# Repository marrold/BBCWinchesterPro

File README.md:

# BBCWinchesterPro

A PCB that combines a Raspberry Pi running [PiTubeDirect](https://github.com/hoglet67/PiTubeDirect) and a J.G Harston's [IDE Interface](https://mdfs.net/Info/Comp/BBC/IDE/), intended to emulate the 6502 2nd Processor and Winchester Hard Disk required to run a Level 3 Econet Fileserver on a BBC Micro Model B.

The current revision was designed to test if the theory works rather than a finished product. The long term goal is to place it in a suitably 80's looking enclosure which will probably require some changes to the overall size and mounting holes but perhaps in the meantime the schematics and PCB will be useful to someone.

The schematic is included as a [PDF](Schematic.pdf)

## Whats the ATTiny MCU for?

PiTubeDirect *toggles* the Pi's onboard LED when the Tube is accessed, however I'd like an external LED to pulse with activity. The ATTiny detects a rising or falling edge and pulses the LED for 50ms.

To use this feature you'll need to program the ATTiny and use the [Indigo Alpha 4](https://github.com/hoglet67/PiTubeDirect/releases/tag/indigo-alpha4) revision of PiTubeDirect which supports re-mapping the activity to another GPIO.

Add the following to the end of `cmdline.txt`:
`bcm2708.disk_led_gpio=16`

This is somewhat experimental, the code is crude, and I'm not entirely sure if its detecting every edge when the Tube is at full tilt, but it makes the LED blink convincingly   so its good enough for my requirements.

If you don't want to bother with it, you can bridge pins 2 and 3 of the U5 footprint, indicated on the silkscreen.

## Usage

- It's *highly recommended* to use a 2GB CF Card as modified tools exist to deal with a disc this size
- For information on setting up and using PiTubeDirect, see the projects detailed [Wiki](https://github.com/hoglet67/PiTubeDirect/wiki)
- To use the IDE interface you'll need version [ADFS  v1.33](https://mdfs.net/System/ROMs/Filing/Disk/Acorn/ADFS133) which has been patched for IDE support.
- I also recommend using patched versions of [HDInit](https://mdfs.net/Info/Comp/BBC/IDE/HDInit) and [WFSInit](https://stardot.org.uk/forums/viewtopic.php?p=411297#p411297) that can handle larger discs.
- For instructions on formatting the CF card see the [Wiki](https://github.com/marrold/BBCWinchesterPro/wiki/Formatting-the-Hard-Disk)
- For instructions on setting up the Econet partition, also see the [Wiki](https://github.com/marrold/BBCWinchesterPro/wiki/Initialising-the-Disk-for-a-Level-3-Econet-Fileserver)

## Parts Required

- [PCI slot IDE to Compact Flash Adapter](https://www.amazon.co.uk/gp/product/B0913811PP)
- Raspberry Pi + SD Card
- 5x 0.1uF ceramic capacitors with a 5mm pitch
- 2x 22uF electrolytic capacitors with a 2mm pitch
- 3x 1k 1/4w resistors
- 3x LEDs and suitable 1/4w resistors
- 2x [SN74LVC245AN](http://d.digikey.com/dc/mn-w0iJh4uEE_bUitNCuXpPSTLmwSDrmPaa_ksuLmn07WQWvHI6vieAM8l8Rz71y9-o2iqNxD_lrRHs2f6p78UOWSMZi80Re0OX4QjTHXhzXzyCP1n-WYmlf5x2yjzHYfHzZC5O6tAVstkKuOzoHwbgnRBw45ztk-WaaeLEz83g=/MDI4LVNYSy01MDcAAAGQeWyQoGkputw3nr4VpWGkNsxv4PB3VXIkOks0B2FcjYxorqdoh39jE906jV2IX0SxzNbf8sc=)
- 1x [SN74LS02N](http://d.digikey.com/dc/mn-w0iJh4uEE_bUitNCuXpPSTLmwSDrmPaa_ksuLmn07WQWvHI6vieAM8l8Rz71y9-o2iqNxD_lrRHs2f6p78bnTDQXV0_ONXEKM5iC55d-ZDkkt9n89zQITQIYKv5ImfzPp6AZ2aezEFJFPNdnpA2yuf_bsGcfQkRQfUysnwfE=/MDI4LVNYSy01MDcAAAGQeWyQoGkputw3nr4VpWGkNsxv4PB3VXIkOks0B2FcjYxorqdoh39jE906jV2IX0SxzNbf8sc=)
- 1x [SN74LS139AN](http://d.digikey.com/dc/mn-w0iJh4uEE_bUitNCuXpPSTLmwSDrmPaa_ksuLmn07WQWvHI6vieAM8l8Rz71y9-o2iqNxD_lrRHs2f6p78ZChZSCAtt8kdLK_f7oz0DTUWDhmkEZ-6cGHutOkHit2hcfdb0F0ck6e2jeWpSL4i42dJ505bw-7yi25-H_klbc=/MDI4LVNYSy01MDcAAAGQeWyQoGkputw3nr4VpWGkNsxv4PB3VXIkOks0B2FcjYxorqdoh39jE906jV2IX0SxzNbf8sc=)
- 1x [ATTINY85-20PU](http://d.digikey.com/dc/mn-w0iJh4uEE_bUitNCuXpPSTLmwSDrmPaa_ksuLmn3wb489Ozp7P-auFeMYVOl116EiIEbZ38BDQy1OX_LrrLPV3Ec8LFvckgIt5WBiMOWBzA2AtKbyb9r8UKNGoR5mw2eYflZHiaYFx4eLpeBZ2Q5_0KFzTh_zHWoZHqgDAwE=/MDI4LVNYSy01MDcAAAGQeWyQoGkputw3nr4VpWGkNsxv4PB3VXIkOks0B2FcjYxorqdoh39jE906jV2IX0SxzNbf8sc=)
- 2x 20 pin DIP sockets
- 1x 16 pin DIP socket
- 1x 14 pin DIP socket
- 1x 4 pin DIP socket
- 1x 40 Pin, 2.54 pitch Male Shrouded + Keyed connector
-  1x 34 Pin, 2.54 pitch  Male Shrouded + Keyed connector
- 1x 40 Pin, 2.54 pitch Female connector with key
- 1x 40 Pin, 2.54 pitch  Female connector without key. (Or get 2 of the above)
- 2.54 pitch male header pins - a few
- 2x Jumpers
- Nylon PCB standoffs - some

## Future improvements
- The Raspberry Pi SD card is blocked by the CF adapter, so upgrading PiTubeDirect requires removing the Pi entirely which isn't great. The Tube and IDE sections of the board should probably be swapped.
- The PCB was designed for a specific IDE to CompactFlash adapter which has resulted in the pin numbering being backwards, making it unsuitable for use with cables or other adapters. In a future revision I'd like to use a standard pin numbering for greater flexibility
- There's no power available on pin 20 of the IDE connector, which some CF adapters can utilise. In future revision it's probably sensible to make power available on this pin with a solder jumper to enable it.

## License

- The PCB is licensed under GPL 3.0
- The [PiTubeDirect](https://github.com/hoglet67/PiTubeDirect) interface schematic and firmware is licensed under GPL 3.0
- The [IDE interface](https://mdfs.net/Info/Comp/BBC/IDE/) was designed by J.G Harston and [sprow](http://www.sprow.co.uk/) and anyone is permitted to use the design with acknowledgement.

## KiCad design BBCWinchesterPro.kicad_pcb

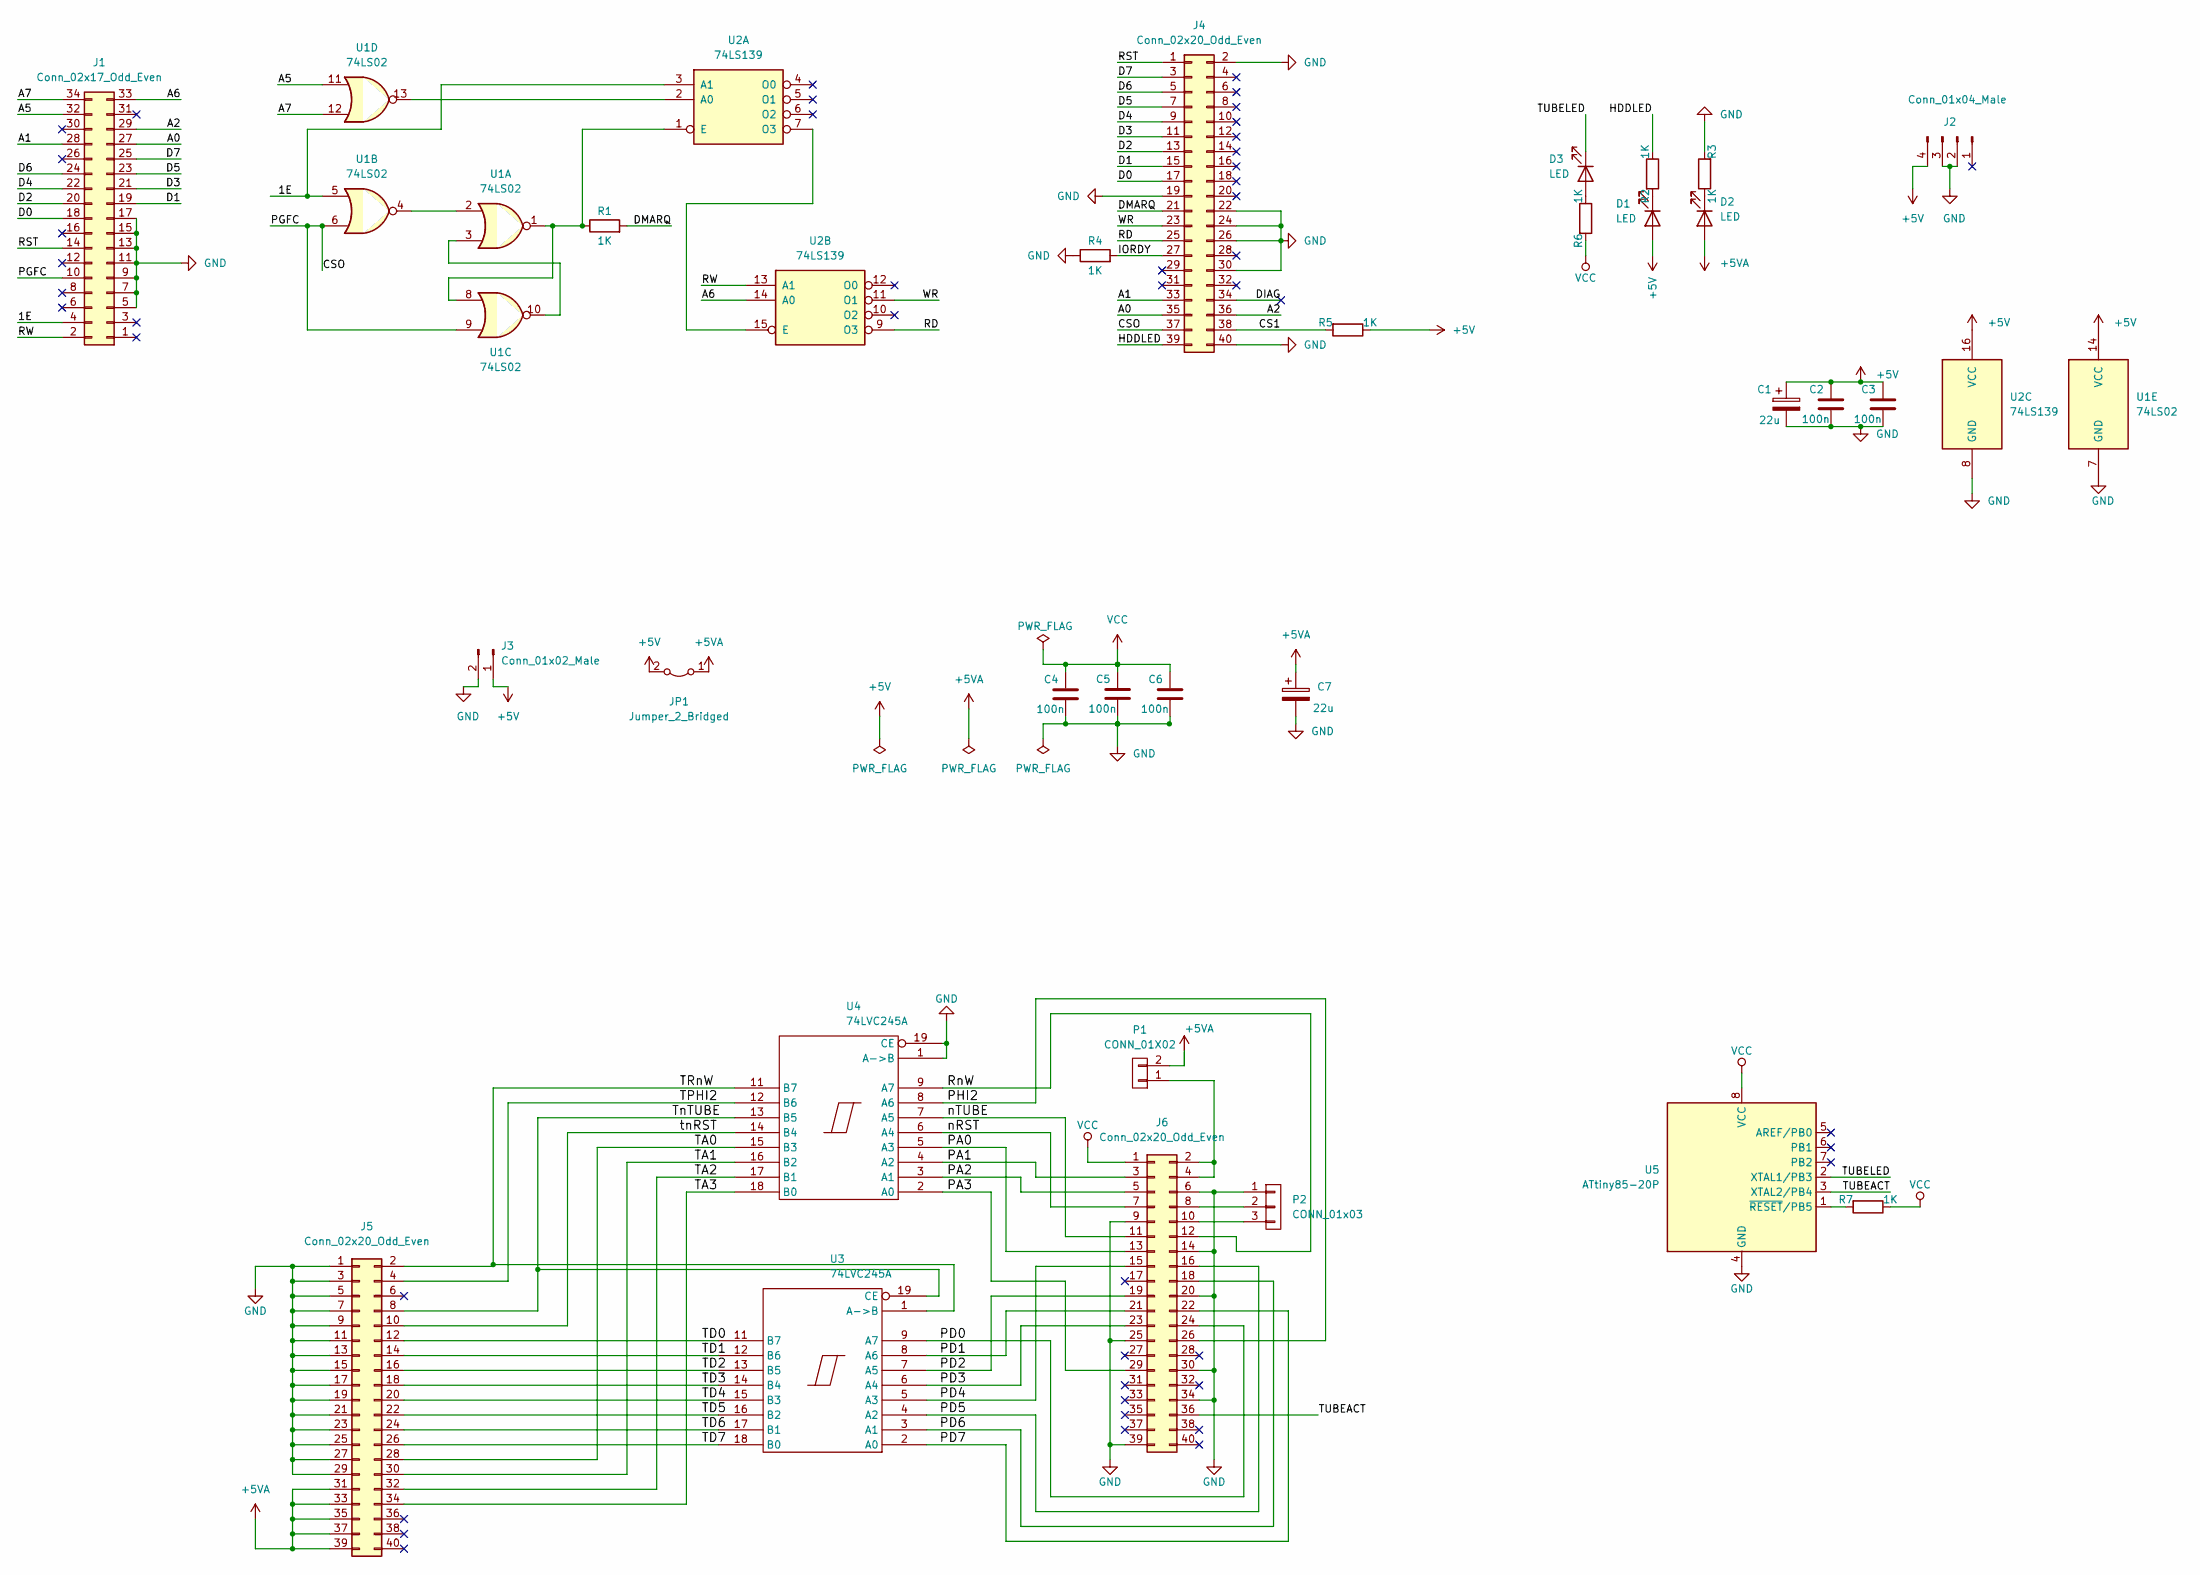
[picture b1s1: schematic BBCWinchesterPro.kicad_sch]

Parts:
C1, C7: 22u; CP_Radial_D5.0mm_P2.00mm
C2, C4, C5, C6: 100n; C_Rect_L7.0mm_W2.5mm_P5.00mm
C3: 100n; C_Rect_L7.0mm_W2.0mm_P5.00mm
D1, D2, D3: LED; PinHeader_1x02_P2.54mm_Vertical
J1: Conn_02x17_Odd_Even; IDC-Header_2x17_P2.54mm_Vertical
J2: Conn_01x04_Male; PinHeader_1x04_P2.54mm_Vertical
J3: Conn_01x02_Male; PinHeader_1x02_P2.54mm_Vertical
J4: Conn_02x20_Odd_Even; CF-Adapter
J5: Conn_02x20_Odd_Even; IDC-Header_2x20_P2.54mm_Vertical
J6: Conn_02x20_Odd_Even; Raspberry_Pi_Zero_Socketed_THT_FaceDown_MountingHoles
JP1: Jumper_2_Bridged; PinHeader_1x02_P2.54mm_Vertical
P1: CONN_01X02; PinHeader_1x02_P2.54mm_Vertical
P2: CONN_01x03; PinHeader_1x03_P2.54mm_Vertical
R1, R2, R3, R4, R5, R6, R7: 1K; R_Axial_DIN0207_L6.3mm_D2.5mm_P7.62mm_Horizontal
U1: 74LS02; DIP-14_W7.62mm_Socket
U2: 74LS139; DIP-16_W7.62mm_Socket
U3, U4: 74LVC245A; DIP-20_W7.62mm_Socket
U5: ATtiny85-20P; DIP-8_W7.62mm

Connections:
+5V: C1.1, C2.1, C3.1, D1.2 (A), J2.4, J3.1, JP1.2 (B), R5.1, U1.14 (VCC), U2.16 (VCC)
+5VA: C7.1, D2.2 (A), J5.31, J5.33, J5.35, J5.37, J5.39, JP1.1 (A), P1.2
/1E: J1.4, U1.5, U2.3 (A1)
/A0: J1.27, J4.35
/A1: J1.28, J4.33
/A2: J1.29, J4.36
/A5: J1.32, U1.11
/A6: J1.33, U2.14 (A0)
/A7: J1.34, U1.12
/CS1: J4.38, R5.2
/CSO: J1.10, J4.37, U1.6, U1.9
/D0: J1.18, J4.17
/D1: J1.19, J4.15
/D2: J1.20, J4.13
/D3: J1.21, J4.11
/D4: J1.22, J4.9
/D5: J1.23, J4.7
/D6: J1.24, J4.5
/D7: J1.25, J4.3
/DIAG: J4.34
/DMARQ: J4.21, R1.2
/HDDLED: J4.39, R2.1
/IORDY: J4.27, R4.2
/PA0: J6.13, U4.5 (A3)
/PA1: J6.3, U4.4 (A2)
/PA2: J6.5, U4.3 (A1)
/PA3: J6.29, U4.2 (A0)
/PD0: J6.24, U3.9 (A7)
/PD1: J6.21, U3.8 (A6)
/PD2: J6.19, U3.7 (A5)
/PD3: J6.23, U3.6 (A4)
/PD4: J6.15, U3.5 (A3)
/PD5: J6.16, U3.4 (A2)
/PD6: J6.18, U3.3 (A1)
/PD7: J6.22, U3.2 (A0)
/PHI2: J6.26, U4.8 (A6)
/RD: J4.25, U2.9 (O3)
/RST: J1.14, J4.1
/RW: J1.2, U2.13 (A1)
/RnW: J6.12, U4.9 (A7)
/TA0: J5.28, U4.15 (B3)
/TA1: J5.30, U4.16 (B2)
/TA2: J5.32, U4.17 (B1)
/TA3: J5.34, U4.18 (B0)
/TD0: J5.12, U3.11 (B7)
/TD1: J5.14, U3.12 (B6)
/TD2: J5.16, U3.13 (B5)
/TD3: J5.18, U3.14 (B4)
/TD4: J5.20, U3.15 (B3)
/TD5: J5.22, U3.16 (B2)
/TD6: J5.24, U3.17 (B1)
/TD7: J5.26, U3.18 (B0)
/TPHI2: J5.4, U4.12 (B6)
/TRnW: J5.2, U3.1 (A->B), U4.11 (B7)
/TUBEACT: J6.36, U5.3 (XTAL2/PB4)
/TUBELED: D3.1 (K), U5.2 (XTAL1/PB3)
/TnTUBE: J5.8, U3.19 (CE), U4.13 (B5)
/WR: J4.23, U2.11 (O1)
/nRST: J6.7, U4.6 (A4)
/nTUBE: J6.11, U4.7 (A5)
/tnRST: J5.10, U4.14 (B4)
GND: C1.2, C2.2, C3.2, C4.2, C5.2, C6.2, C7.2, J1.5, J1.7, J1.9, J1.11, J1.13, J1.15, J1.17, J2.2, J2.3, J3.2, J4.2, J4.19, J4.22, J4.24, J4.26, J4.30, J4.40, J5.1, J5.3, J5.5, J5.7, J5.9, J5.11, J5.13, J5.15, J5.17, J5.19, J5.21, J5.23, J5.25, J5.27, J5.29, J6.6, J6.9, J6.14, J6.20, J6.25, J6.30, J6.34, J6.39, P2.1, R3.2, R4.1, U1.7 (GND), U2.8 (GND), U3.10 (GND), U4.1 (A->B), U4.10 (GND), U4.19 (CE), U5.4 (GND)
unnamed: D1.1 (K), R2.2
unnamed: D2.1 (K), R3.1
unnamed: D3.2 (A), R6.1
unnamed: J6.2, J6.4, P1.1
unnamed: J6.8, P2.2
unnamed: J6.10, P2.3
unnamed: R1.1, U1.1, U1.8, U2.1 (E)
unnamed: U1.2, U1.4
unnamed: U1.3, U1.10
unnamed: U1.13, U2.2 (A0)
unnamed: U2.7 (O3), U2.15 (E)
unnamed: R7.2, U5.1 (~RESET/PB5)
VCC: C4.1, C5.1, C6.1, J6.1, R6.2, R7.1, U3.20 (VCC), U4.20 (VCC), U5.8 (VCC)

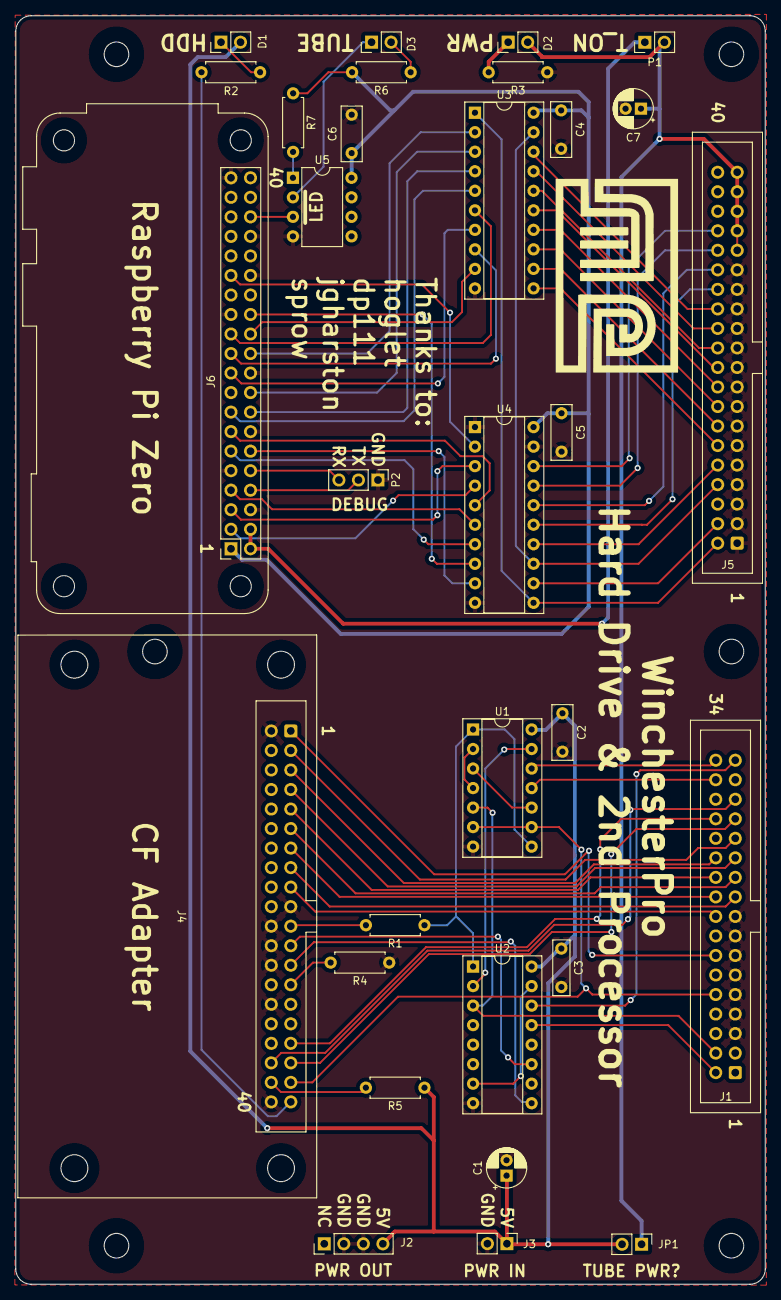
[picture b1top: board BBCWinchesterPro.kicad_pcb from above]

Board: 2 copper layers, 97.5 x 165.0 mm, 31 parts (0 on the bottom side), 74 nets.

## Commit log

2024-01-03 init
2024-01-03 Fix DRC
2024-01-18 Update license
2024-01-19 Add ATTiny code and remove license from silkscreen
2024-01-21 Update README, include image
2024-01-21 Annotate schematic and export as PDF
2024-01-21 README formatting
2024-01-23 Add wiki images
2024-01-23 Add WFSINIT images
